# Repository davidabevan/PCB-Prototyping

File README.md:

# PCB-Prototyping
Eagle Cad/Fritzing Footprints for hard to find parts.

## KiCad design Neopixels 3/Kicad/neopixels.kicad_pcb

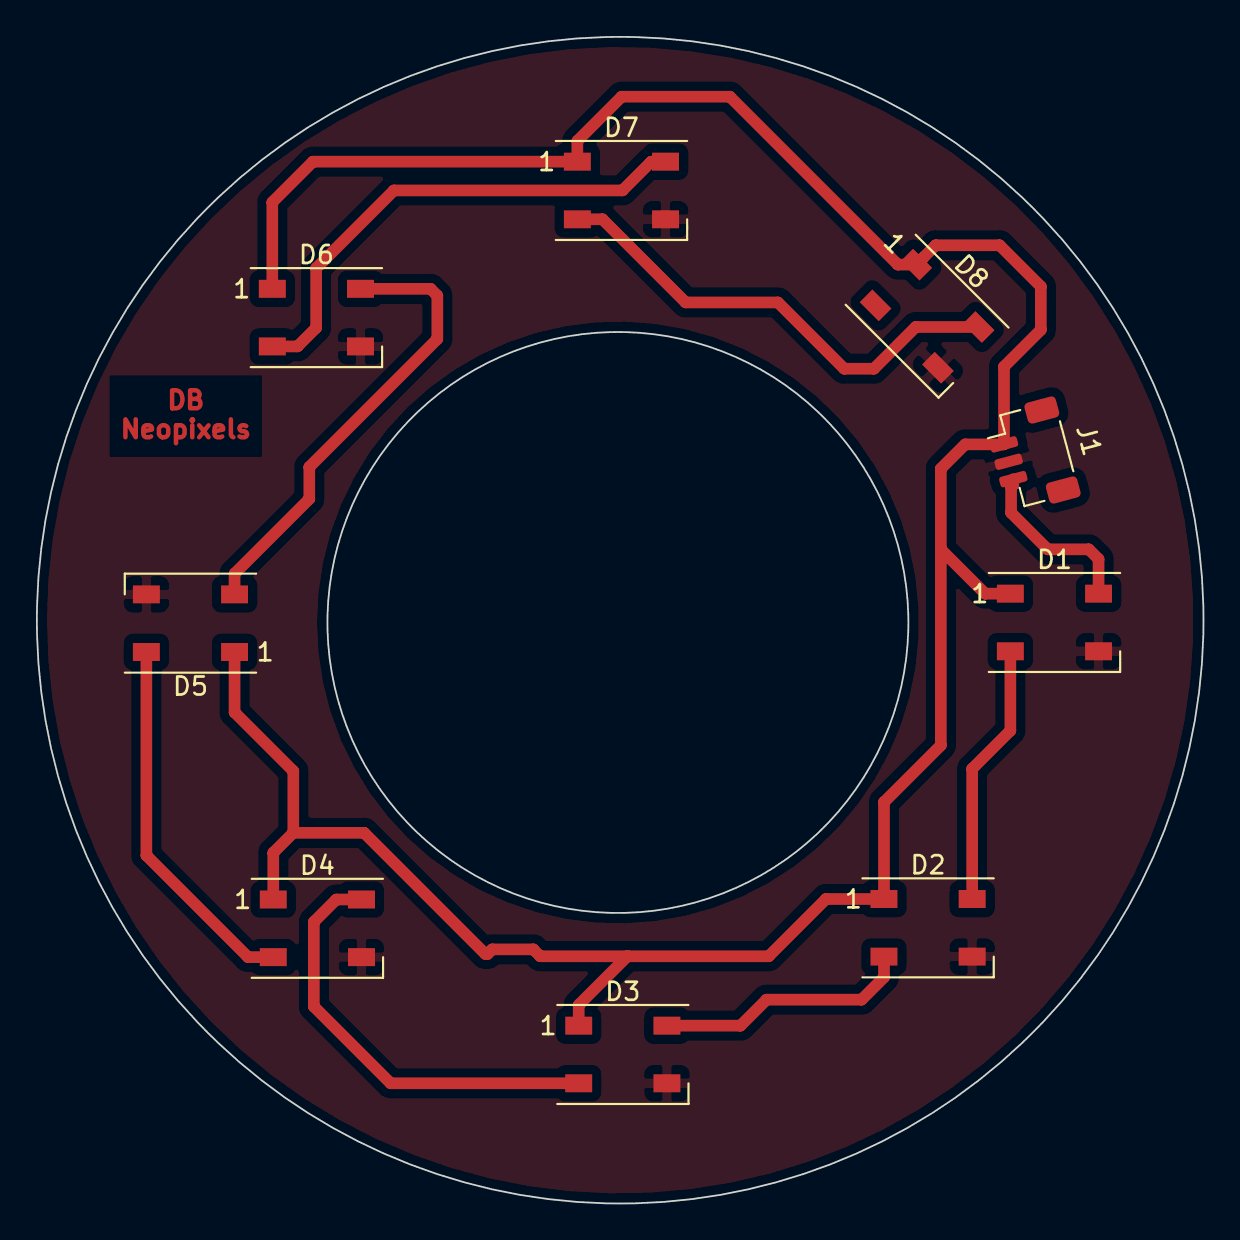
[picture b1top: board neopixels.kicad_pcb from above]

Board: 2 copper layers, 64.8 x 64.8 mm, 9 parts (0 on the bottom side), 10 nets.

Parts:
D1, D2, D3, D4, D5, D6, D7, D8: WS2812B; LED_WS2812B_PLCC4_5.0x5.0mm_P3.2mm
J1: Conn_01x03_Female; JST_SH_BM03B-SRSS-TB_1x03-1MP_P1.00mm_Vertical

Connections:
+5V: D1.1, D2.1, D3.1, D4.1, D5.1, D6.1, D7.1, D8.1, J1.1
GND: D1.3, D2.3, D3.3, D4.3, D5.3, D6.3, D7.3, D8.3, J1.2
unnamed: D1.2, D2.4
unnamed: D1.4, J1.3
unnamed: D2.2, D3.4
unnamed: D3.2, D4.4
unnamed: D4.2, D5.4
unnamed: D5.2, D6.4
unnamed: D6.2, D7.4
unnamed: D7.2, D8.4

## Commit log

2019-01-17 contains Arduino ssd1306
2019-01-17 added attiny 85
2019-01-17 added cr2032 holder
2019-01-18 added sparkfun drc and cam files
2019-01-20 Create Home etched boards
2019-01-20 Update Home etched boards
2019-01-21 New ATTiny85 Board design
2019-01-23 created my own esp32 dev board footprint for the 36
2019-01-24 MY NEW VERSION CORRECTED PINS FOR 38 PIN DEV BOARD
2019-02-03 3d version made
2019-02-10 My Managed library
    Added 3d parts work in progress
    Added Silkscreen to 2.2 TFT spi display
2019-02-10 Removed False diameter dimension from silkscreen
2020-02-26 New ws28112b Board
2020-02-26 WS28112b RGB Breakout board single
2020-02-26 Add files via upload
    revised corrected pinouts sh version
2020-03-01 Create Kicad Projects
2020-03-01 kicad circular ws2812b board
2020-03-01 Updated library March 2020
2020-03-09 Places ws2112b leds in a circle decided by radius and led count
